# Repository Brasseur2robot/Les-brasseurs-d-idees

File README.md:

# Codebase des brasseurs d'idées

## Description

Codebase de l'équipe légende des brasseurs d'idées concourant à la coupe de France de robotique. Vous pouvez y retrouver les différents fichiers utilisés pour la création et le fonctionnement de notre robot principal et de nos PAMI.

## Historique

- [2025](https://github.com/Brasseur2robot/Les-brasseurs-d-idees/tree/2025)

## Palmarès

- 2025 : 25ème au classement général et 9ème classement Légendes
- 2026 : 48ème au classement général et 18ème classement Légendes

## Lidar
Le STL27L : [doc ici](https://www.waveshare.com/wiki/DTOF_LIDAR_STL27L) Avec le programme de test "LdsPointCloudViewer" dispo sur le lien. Il y a aussi un bête programme pour juste démarrer/arrêter le Lidar à partir d'un esp.
Un [projet](https://github.com/kaiaai/LDS/blob/main/README.md) qui supporte pas mal de Lidar différent (mais pas le notre). Cela semble une bonne base de départ.

## Telemétrie et debug
[Ici](https://git.poivron-robotique.fr/Keuronde/ESP32_Teleplot/src/branch/master/ESP32_Teleplot.ino) un projet tout simple pour envoyer par wifi des paquets UDP à un serveur Teleplot (pour un uC ESP-32).

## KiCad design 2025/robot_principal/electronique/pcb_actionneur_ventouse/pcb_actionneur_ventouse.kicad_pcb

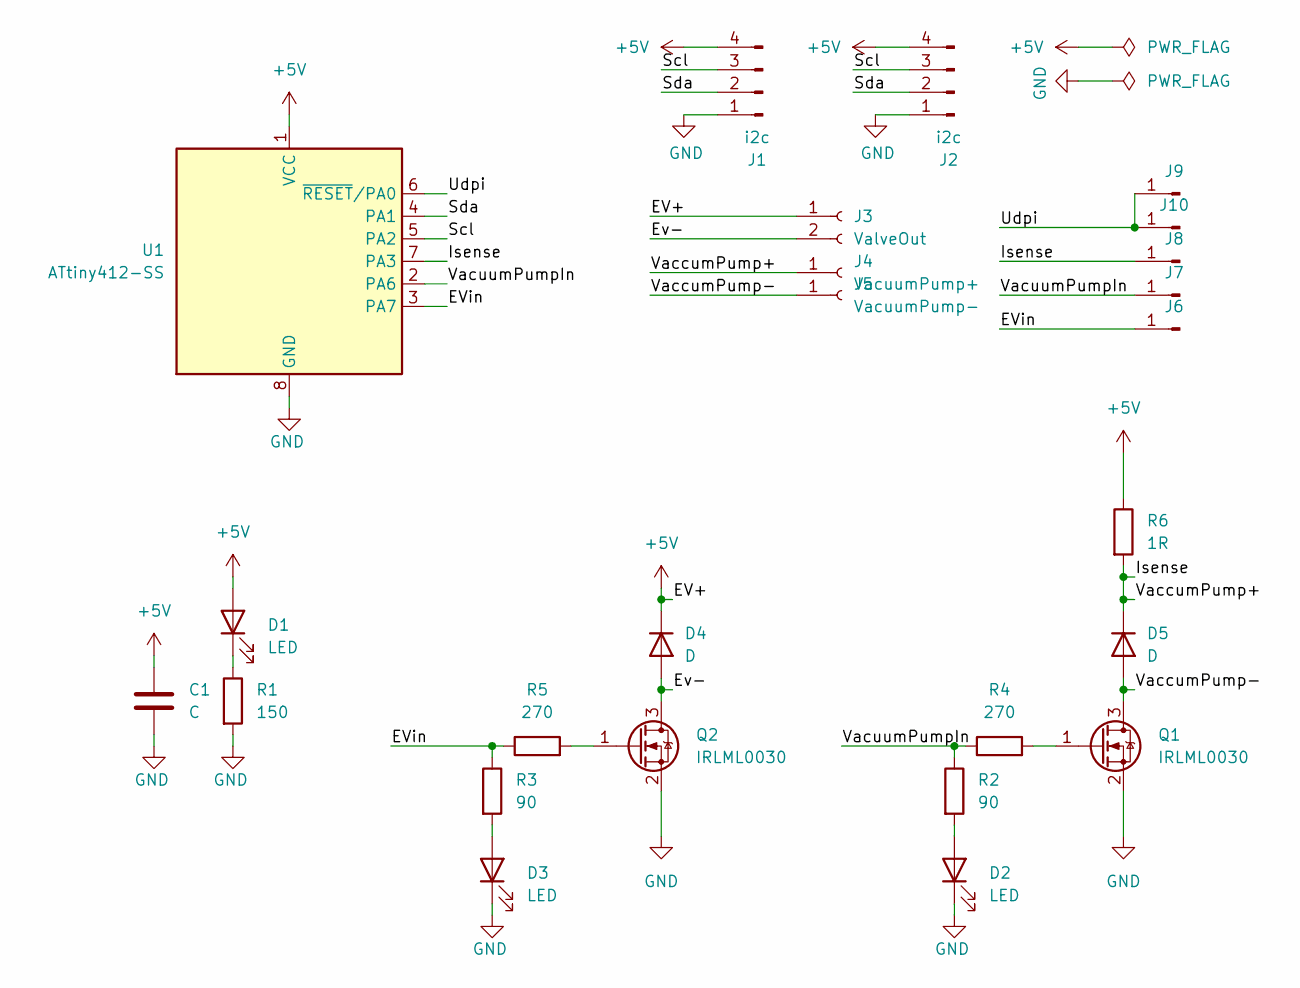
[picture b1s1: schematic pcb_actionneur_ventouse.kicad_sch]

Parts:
C1: C; C_0603_1608Metric_Pad1.08x0.95mm_HandSolder
D1, D2, D3: LED; D_0603_1608Metric_Pad1.05x0.95mm_HandSolder
D4, D5: D; D_SOD-123
J1, J2: i2c; PinHeader_1x04_P2.54mm_Vertical
J3: ValveOut; PinHeader_1x02_P2.54mm_Vertical
J4: VacuumPump+; MountingHole_2.5mm_Pad_TopBottom
J5: VacuumPump-; MountingHole_2.5mm_Pad_TopBottom
J6, J7, J8, J9: Conn_01x01_Pin; SolderWirePad_1x01_SMD_1x2mm
J10: Conn_01x01_Pin; PinSocket_1x01_P2.54mm_Vertical
Q1, Q2: IRLML0030; SOT-23
R1: 150; R_0603_1608Metric_Pad0.98x0.95mm_HandSolder
R2, R3: 90; R_0603_1608Metric_Pad0.98x0.95mm_HandSolder
R4, R5: 270; R_0603_1608Metric_Pad0.98x0.95mm_HandSolder
R6: 1R; R_1206_3216Metric_Pad1.30x1.75mm_HandSolder
U1: ATtiny412-SS; SOIC-8_3.9x4.9mm_P1.27mm

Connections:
+5V: C1.1, D1.2 (A), D4.1 (K), J1.4, J2.4, J3.1, R6.1, U1.1 (VCC)
/EVin: J6.1, R3.1, R5.1, U1.3 (PA7)
/Ev-: D4.2 (A), J3.2, Q2.3 (D)
/Isense: D5.1 (K), J4.1, J8.1, R6.2, U1.7 (PA3)
/Scl: J1.3, J2.3, U1.5 (PA2)
/Sda: J1.2, J2.2, U1.4 (PA1)
/Udpi: J9.1, J10.1, U1.6 (~RESET/PA0)
/VaccumPump-: D5.2 (A), J5.1, Q1.3 (D)
/VacuumPumpIn: J7.1, R2.1, R4.1, U1.2 (PA6)
GND: C1.2, D2.1 (K), D3.1 (K), J1.1, J2.1, Q1.2 (S), Q2.2 (S), R1.2, U1.8 (GND)
unnamed: D1.1 (K), R1.1
unnamed: D2.2 (A), R2.2
unnamed: D3.2 (A), R3.2
unnamed: Q1.1 (G), R4.2
unnamed: Q2.1 (G), R5.2

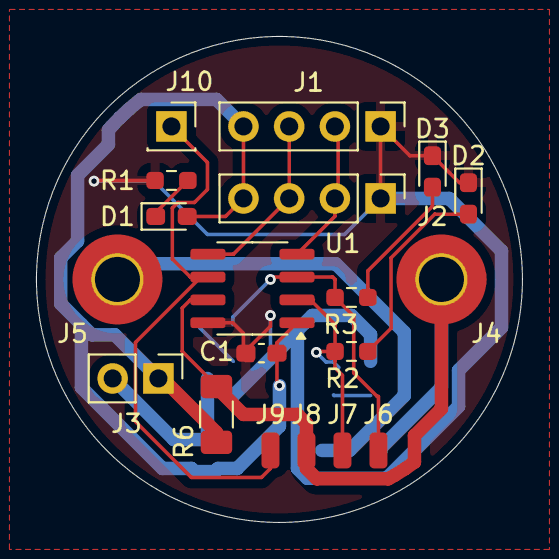
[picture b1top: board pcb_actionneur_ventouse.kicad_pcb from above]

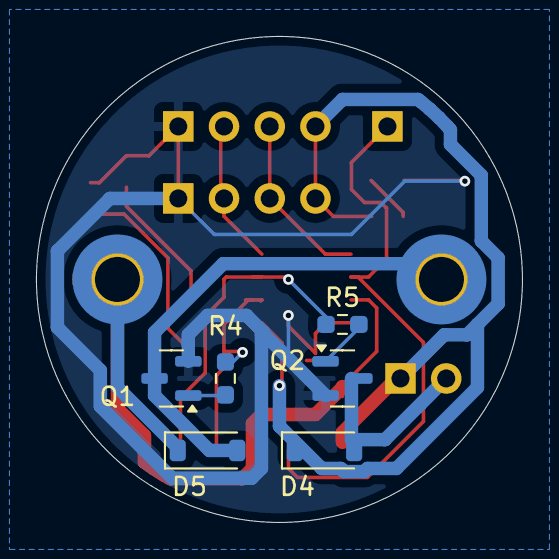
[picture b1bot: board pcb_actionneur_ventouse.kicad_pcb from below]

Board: 2 copper layers, 27.0 x 27.0 mm, 25 parts (6 on the bottom side), 15 nets.

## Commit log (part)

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2024-10-27 Ajout README et dossier 2025
2024-10-29 typo
2024-10-29 Converted the pid module to use structures, so that the functions are rationalized. Impacted the init of the pids, which is now in the position manager init and not in the main.
2024-10-29 Converted the ramp module to use structures. Allowed to have a ramp in distance and a ramp in orientation.
2024-10-29 Adapted the config files structure to adapt for several robots.
2024-10-30 cleaned up config_meca file and added explanations
2024-10-30 prevents multi inclusion of config files
2024-10-30 cleaned up config_pin.h
2024-10-30 moved all robot dependent parameter to a separate config_control.h file in order to tune the controller for each robot
2024-10-30 fix : forgot one include
2024-10-30 Added the correction factors for distance and orientation. Moved the pids debug on the position manager level.
2024-10-30 Merged the calibration square trajectory cw and ccw into one function, with a boolean argument to differentiate both cases
2024-10-30 fix the ramp module for consecutive ramps
2024-10-30 Groundwork for the pami calibration
2024-10-30 More groundwork for the pami calibration. Calibration not satisfying at the moment
2024-10-30 Added input definition for reed and ground switch. Reed switch not working at the moment.
2024-10-31 Moved the trajectory code in its own manger. Groundwork for a trajectory manager done.
2024-11-01 Code clean up.
2024-11-01 Refactored position_mgr to get a state (enum) and not only a binary value. Allows trajectory to distinguish between moving/stopped/emergency. Increased threshold on obstacle sensor.
2024-11-23 First version of trajectory
2024-11-24 added test function for encoder and motor
2024-12-02 add ihm support with different display screens on Oled.
2024-12-03 add debug motor and debug control screen in ihm. added match manager.
2024-12-07 Adding switch case to the position system
2024-12-14 Create LICENSE
2024-12-29 Tested configuration for 1 PAMI with multiple trajectory
2025-01-04 Too long to describe. Ihm screen added, match manger reworked to calibrate starting position and waiting time at match start. Various fixes in the other files
2025-01-06 Added the second PAMI to the config files
2025-01-06 Moved a control parameter from config.h to config_control.h
2025-01-06 Added the actuator manager which controls only the serbo on the PAMI. Integrated the servo start at the end of the match. Headbang is coming!
2025-01-06 Added debug messages to servo actuator
2025-01-07 Moved constant in the code to define for servo speed.
2025-01-07 Added a sensor module which currently only reads Vbatt. Dedicate LED_2 as Vbatt level indicator. Reworked the sensor obstacle blink code on LED_4.
2025-01-08 corrected Vbatt level and added missing time control! Numerous loops were repeated too much!
2025-01-19 enhanced debug
2025-01-19 First try of evasion & minor bugs correction
2025-01-19 Realign to main branch (#3)
    * Add 3d files via upload
    * Added the second PAMI to the config files
    * Moved a control parameter from config.h to config_control.h
    * Added the actuator manager which controls only the serbo on the PAMI. Integrated the servo start at the end of the match. Headbang is coming!
    * Added debug messages to servo actuator
    * Moved constant in the code to define for servo speed.
2025-01-19 Patch test for evasion
2025-01-24 change to pami 2
2025-02-02 introduction of pose struct
2025-02-02 Adding all PAMI in config_match
2025-02-02 Updating trajectory branch with main branch (#4)
    * Updating trajectory from main
    ---------
2025-02-09 Updating trajectory_mgr to work with an array of Position (PoseStruct). Still need to be polished because only the PAMI_1 works fine.
2025-03-22 Setting all PAMI trajectory and more specifically the one for PAMI 1
2025-03-30 Adding a new border calibration, new trajectory (forgotten in the last commit), new config_meca for the PAMI 1
2025-04-16 Create Robot principal
2025-04-27 odometry fix. Reset the orientation of the robot actually works now. Included config for PAMI_3.
2025-05-08 Adjusting the odometry reset
2025-05-18 Evasion is finished, but odometry still not perfect
2025-05-25 First commit of pcbs and src for robot
2025-05-28 Robot trajectory evolution (goto xytheta)
2025-05-28 Trajectory for both sides added. Problem of set theta solved (I think :D )
2025-05-28 Added the obstacle sensor code. Corrected starting point for both sides.
2025-05-29 Added the actuator parameter and the catch
2025-05-29 Advanced configuration for match
2025-05-29 Trajectory merged to main branch (#5)
    * Evasion is finished, but odometry still not perfect
    * Advanced configuration for match
2025-05-29 Added an first base of an event manager
2025-05-30 Patching set theta (in odometry) for PAMI and cleaning headers
2025-06-01 Modded actuator to cope with stepper signal generation. Modified the robot trajectory. Final commit during coupe de france 2025.
2025-06-05 Final version for 2025
2025-06-07 Final version for 2025
    * Patching set theta (in odometry) for PAMI and cleaning headers
    * Final version for 2025
2025-06-08 New file architecture
2025-06-08 Updating the README
2025-07-21 Retired old stepper code. Added Dynamixel code and ihm menu system
2025-10-28 Preliminary support of TMC2209 stepper drivers
2025-11-02 Converted motor.cpp to use the new driver logic (only one dir pin and one pwm pin per motor). Added a submenu to test motors
2025-11-06 Reworked the motor interface with ledc API for PWMs. Added controller support for BLE controller.
2025-11-11 Preliminary support of color sensor GY-AS7262. Added a menu entry to initiate color measurement
2025-12-17 PAMI switch to esp32. Preliminary support.Added RGB led, motor config, wifi.
2025-12-18 Convert the pami base to the updated position/trajectory mgr from the robot.Suppressed references to sumo, which is now unused.
2025-12-20 Continued adaptation to nano esp32, with removal of analogWrite and use od EPS32PWM library. Removes the conflict of pwm pre-allocation by arduino nano ESP32.
2025-12-20 Converted everything in meter to centimeter to avoid rounding errors.
2025-12-20 Coherent Led usage for obstacle sensor.
2025-12-20 removed customTimer.
2025-12-20 Reworked color sensor. Added its output in ihm. Expanded wifi com to send color and start signal to PAMIs.
2025-12-21 First lidar dev.
2025-12-22 small changes for pwm speed.
2025-12-27 changed a print into a debug motor. Added init logic to servo_board.
2025-12-28 augmented resolution on encoders by using FullQuad.
2025-12-28 Updated the init prints of each module. Fixed a few bugs for the simulation case of the obstacle sensor. Added a servoboard test entry in the ihm menu.
2025-12-31 expanded the simulation mode to every i2c board/extension but the lcd screen.
2025-12-31 Modified the color choice logic. No dedicated button anymore. Is is accessible through a menu item. Added the control of the lcd screen rgb backlight to reflect the color choice.
2025-12-31 Removed ancient servo control (2025). Added a servo controller with time estimation of the action.
2026-01-02 Separated the simulation define from the no obstacle sensor define.
2026-01-02 Base of the new action mgr. Works like a replica aof the trajectory manager, but for actuators.
2026-01-02 Modified the Next Step state of the action_mgr to do step immediately one after another if needed (when no wait). Added a verification in SetNextAction to see if action mgr can do another action. Fil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
2026-01-02 ServoBoard, changed logic to min and max angle, added a verification of the target asked.
2026-01-02 Changed the start/stop logic for min/max angle logic. Added a menu to test each servo axis within min/max constrains. Added another action to demonstrate eject inverted boxes.
2026-01-03 Added a duration computation based on the speed of the servos. Added a speed property to the servo controller. Modified the previous duration to act as a supplementary delay at the end of the servo m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
2026-01-06 Modified the sdcard to be able to transfer files to robot_mgr. Created robot_mgr to load json file from sdcard, parse it and setup the trajectory.
2026-01-06 Modified Color sensor coded to suppress delay, in order not to block everything while measuring. Now it is in a state machine and has an update function.
2026-01-07 suppressed old pwm frequency adjustement.
2026-01-08 Converted odometry from meters to millimeters. Corrected a bug in error obervation for pid. Corrected a bug in odometry, a global variable was not used.
2026-01-11 Erwan's work on pami start positions and trajectory.
2026-01-11 performance improvement : double to float.
2026-01-12 Bugfix : a global variable in ramp, which was overwritten when multiple ramps are used.
2026-01-12 Modified servo_board to use ramps, to control speed of servo moves.
2026-01-12 Fixed a incorrect division.
2026-01-12 Fixed another bug on the duration computation.
2026-01-12 ServoBoard, Converted double to float.
2026-01-18 Combined both arm left and right servos into a single command in the ihm servo cfg menu.
2026-01-19 Fixed init condition of servos, so that they are driven to the init position. Fixed ramp to compute 10 times the top resolution in int.
2026-01-19 Fixed sim mode for actuator dxl.
2026-04-14 Reworked the us signals for servos. Changed the arm servos with 270°. Speed boost on servos.
2026-04-16 small improvement in motor test to better track the motor's rotation
2026-04-16 Encoder switched to full quadrature, so measuring is twice as precise.
2026-04-17 Fixed the supplementary delay, the overwrite of a new move on an already moving axis, some actions. Added a shutdown function for the servoboard. Added actions, added control to the ihm and to the co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
2026-04-17 added the same behaviour as when starting a match (transport action) when the controller choice is made.
2026-04-23 Added enable property to actuator dxl and servo board to assess availability of the physical actuators.
2026-04-23 Added input check on ioexpander.
2026-04-25 fixed timeout and restart of position mgr.
2026-05-03 feat: integrate ldlidar_stl_ros2 and object_detector as submodule
2026-05-03 feat: integrate ldlidar_stl_ros2 and object_detector as submodule (#8)
2026-05-05 converted to double and added the better timeout logic.
2026-05-06 Modified the waiting logic at the end of a move, to be really at the end of a move.
2026-05-06 fixed the logic of the obstacle sensor.
2026-05-06 Fixed the use of atan2
2026-05-06 Merged trajectory evasion into trajectory and expanded the trajectory mgr states. Fixed a few mistakes in borders.
2026-05-07 Added parameters to emergency move.
2026-05-07 Copied the emergency way of doing from the pami. Improved the waiting timer in match_mgr.
2026-05-07 Adjusted the angle of the cursor arms. Added their control through the controller.
2026-05-10 Added pami grenier (not ready yet). Added Erwan modification to start procedure.
2026-05-11 Added the possibility to use a Lidar. Comm with ping and ask for obstacle position.
2026-05-11 Commented the actuator.cpp file to enable use of Lidar.
2026-05-14 Added PAMI_G support. Added detect deadzone. Added action_mgr.
2026-05-14 Trajectory, timing and servo speed update
2026-05-15 Added waiting state in trajectory_mgr to wait for the action to finish.
2026-05-15 Support of robot 2026. Fixed action_mgr. Tweaked configs. added menus in ihm. Added lidar com support. Began sd strategy support in sdcard and robot_mgr.
2026-06-11 Added a controller module to the pami. Fixed the motor control to high frequency pwm.
2026-06-11 Modified the lidar porject to run on the S3 board. Needs a fix in ld06 library to support the STL-27p lidar.
2026-06-11 Added nogo zones defintion.
2026-06-12 Big Fucking Merge. Never do that again! robot_poc branch into main.
2026-06-13 Follow up of the Big Fucking Merge. clean up of last merge.
2026-06-18 Update README.md
    added the udp teleplot project link

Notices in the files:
README.md:
License: GNU GPLv3
